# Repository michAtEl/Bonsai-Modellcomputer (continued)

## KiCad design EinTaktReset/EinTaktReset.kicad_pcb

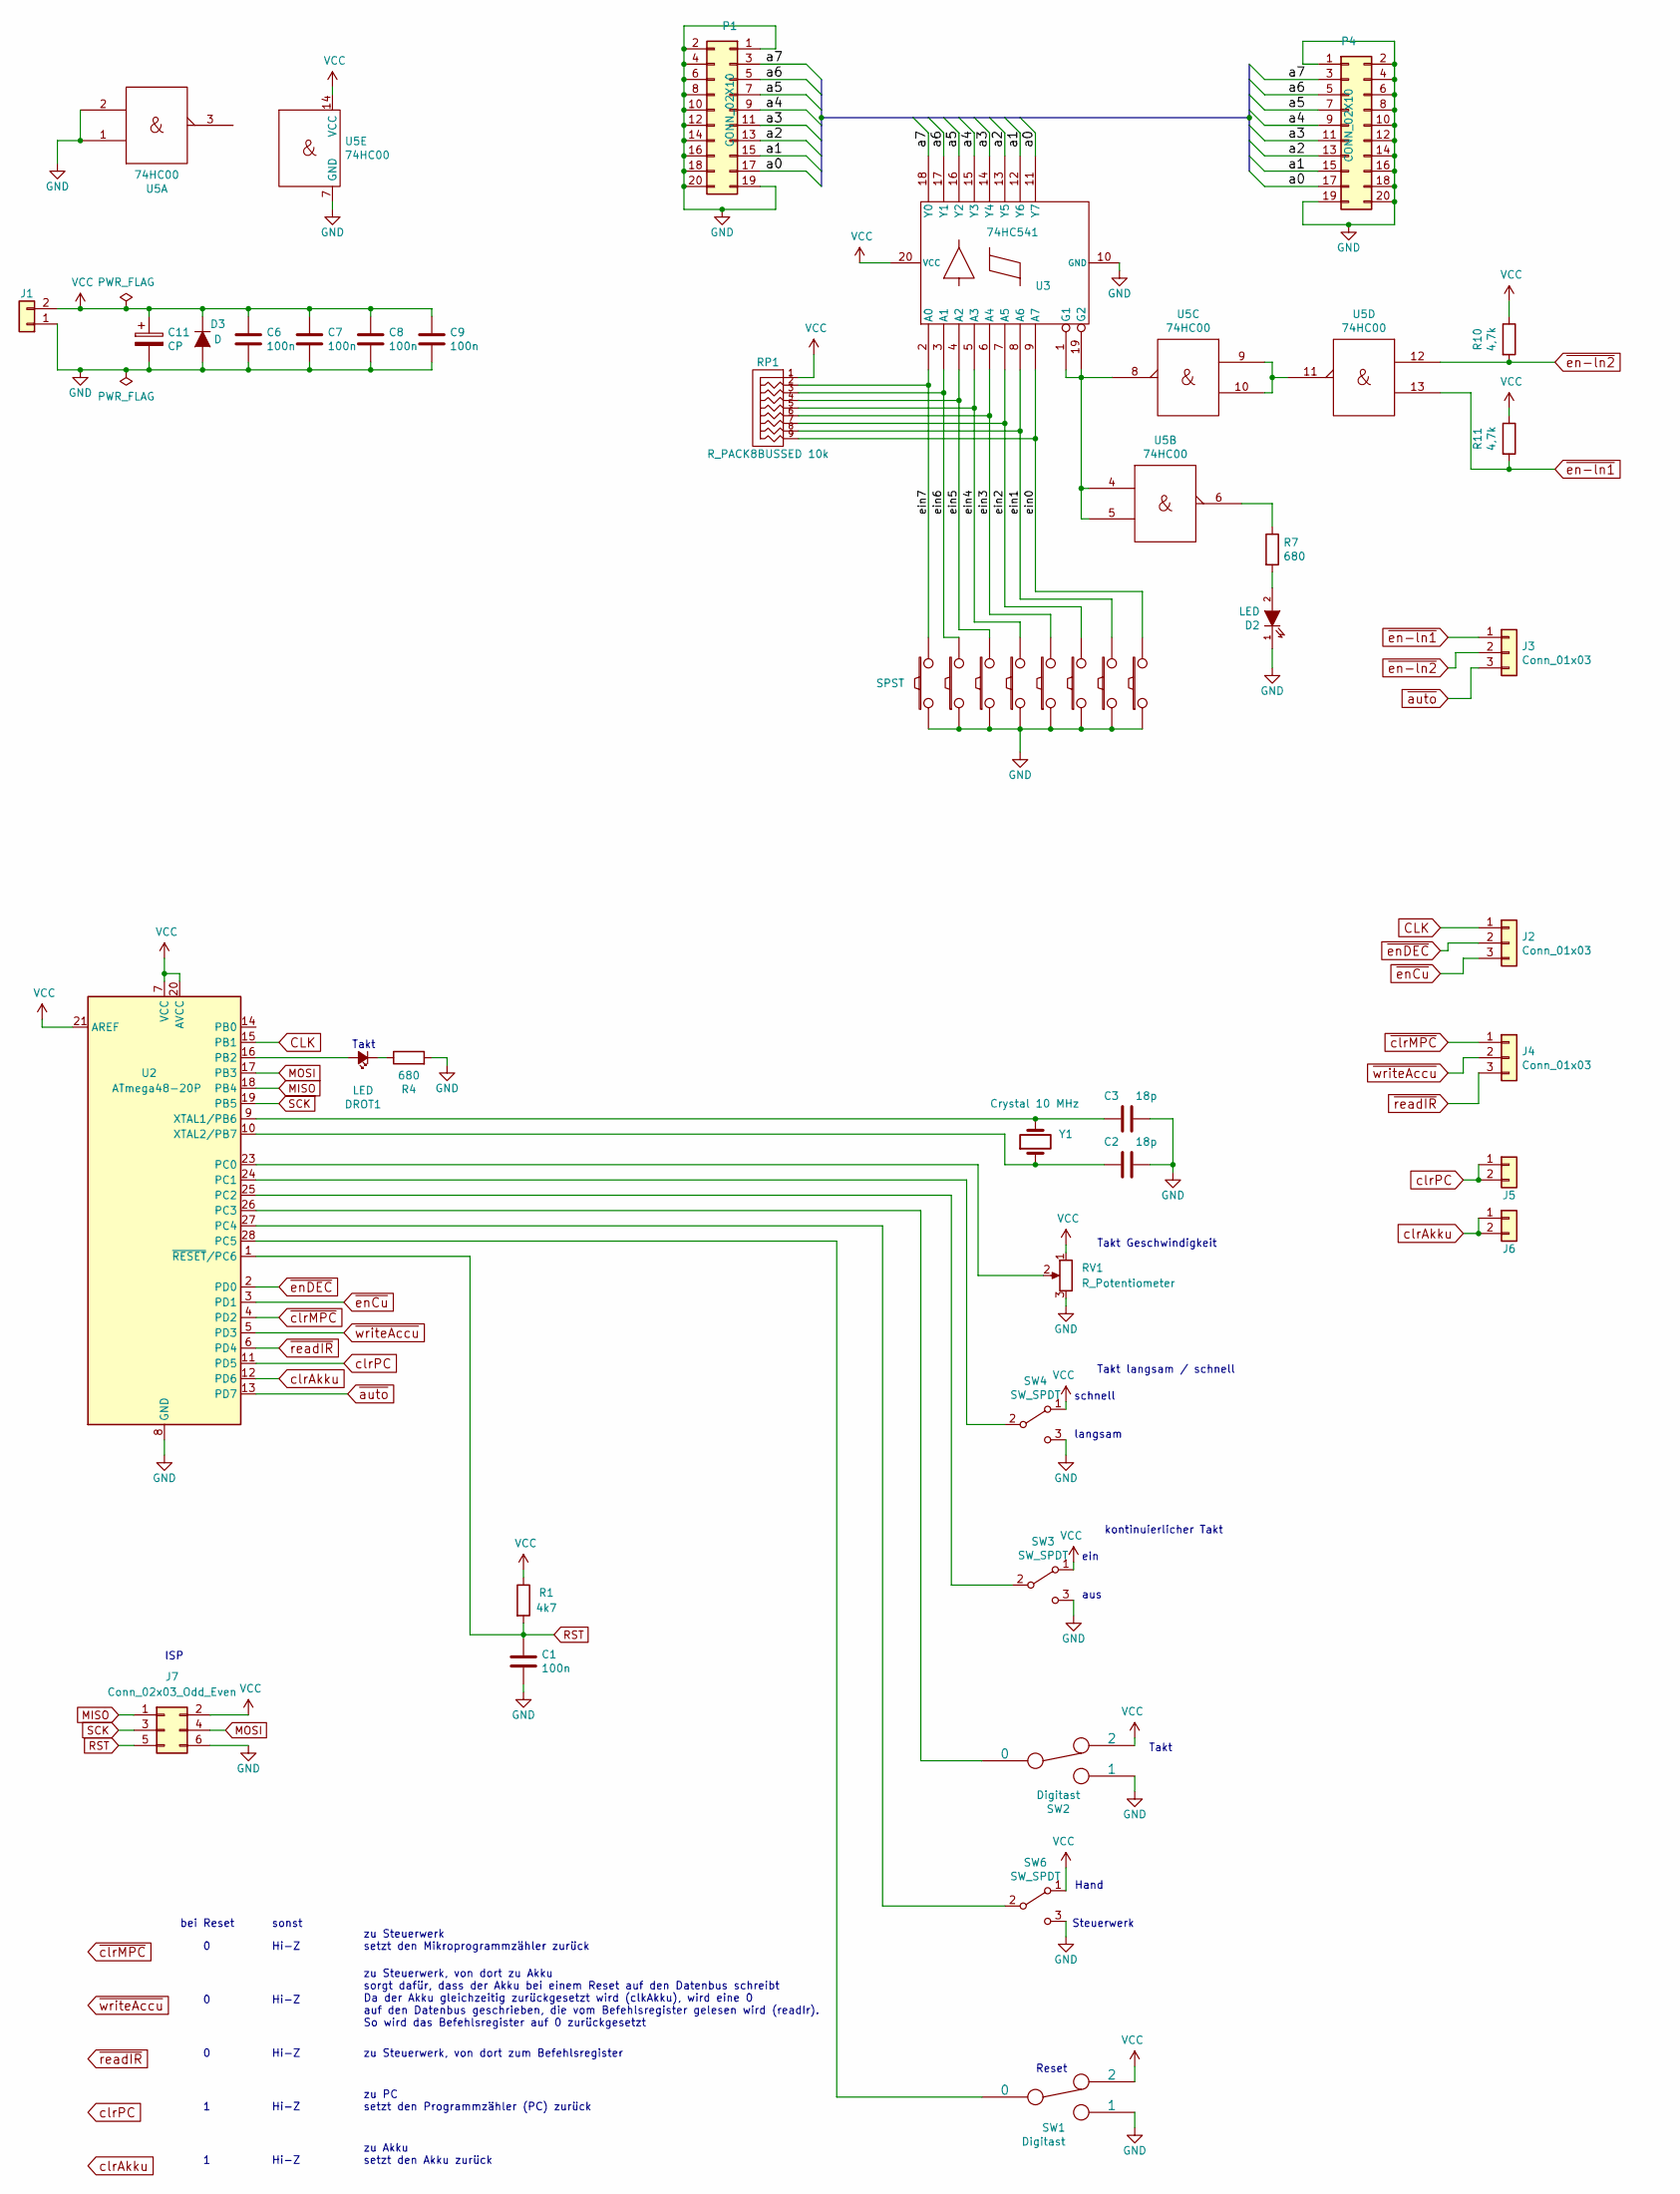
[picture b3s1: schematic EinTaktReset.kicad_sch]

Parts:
C1, C6, C7, C8, C9: 100n; C_Disc_D10.0mm_W2.5mm_P5.00mm
C2, C3: 18p; C_Disc_D3.8mm_W2.6mm_P2.50mm
C11: CP; CP_Radial_D8.0mm_P2.50mm
D2: LED; LED_D3.0mm
D3: D; D_A-405_P10.16mm_Horizontal
DROT1: LED; LED_D3.0mm
J1, J5, J6: Conn_01x02; Molex_KK-254_AE-6410-02A_1x02_P2.54mm_Vertical
J2, J3, J4: Conn_01x03; Molex_KK-254_AE-6410-03A_1x03_P2.54mm_Vertical
J7: Conn_02x03_Odd_Even; PinHeader_2x03_P2.54mm_Vertical
P1, P4: CONN_02X10; PinHeader_2x10_P2.54mm_Vertical
R1: 4k7; R_Axial_DIN0207_L6.3mm_D2.5mm_P10.16mm_Horizontal
R4, R7: 680; R_Axial_DIN0207_L6.3mm_D2.5mm_P10.16mm_Horizontal
R10, R11: 4,7k; R_Axial_DIN0207_L6.3mm_D2.5mm_P10.16mm_Horizontal
RP1: R_PACK8BUSSED 10k; R_Array_SIP9
RV1: R_Potentiometer; Potentiometer_Piher_PT-15-V02_Vertical
SW1, SW2: Digitast; Switch_Digitast
SW3, SW4, SW6: SW_SPDT; switch_100sp5
SW5, SW7, SW8, SW9, SW10, SW11, SW12, SW13: SPST; switch_100sp5
U2: ATmega48-20P; DIP-28_W7.62mm_LongPads
U3: 74HC541; DIP-20_W7.62mm_Socket_LongPads
U5: 74HC00; DIP-14_W7.62mm_Socket_LongPads
Y1: Crystal 10 MHz; Crystal_HC49-U_Vertical

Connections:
/a0: P1.17, P4.17, U3.11 (Y7)
/a1: P1.15, P4.15, U3.12 (Y6)
/a2: P1.13, P4.13, U3.13 (Y5)
/a3: P1.11, P4.11, U3.14 (Y4)
/a4: P1.9, P4.9, U3.15 (Y3)
/a5: P1.7, P4.7, U3.16 (Y2)
/a6: P1.5, P4.5, U3.17 (Y1)
/a7: P1.3, P4.3, U3.18 (Y0)
/ein0: RP1.9, SW13.2, U3.9 (A7)
/ein1: RP1.8, SW12.2, U3.8 (A6)
/ein2: RP1.7, SW11.2, U3.7 (A5)
/ein3: RP1.6, SW10.2, U3.6 (A4)
/ein4: RP1.5, SW9.2, U3.5 (A3)
/ein5: RP1.4, SW8.2, U3.4 (A2)
/ein6: RP1.3, SW7.2, U3.3 (A1)
/ein7: RP1.2, SW5.2, U3.2 (A0)
CLK: J2.1, U2.15 (PB1)
GND: C1.2, C2.2, C3.2, C6.2, C7.2, C8.2, C9.2, C11.2, D2.1 (K), D3.2 (A), J1.1, J7.6, P1.1, P1.2, P1.4, P1.6, P1.8, P1.10, P1.12, P1.14, P1.16, P1.18, P1.19, P1.20, P4.1, P4.2, P4.4, P4.6, P4.8, P4.10, P4.12, P4.14, P4.16, P4.18, P4.19, P4.20, R4.2, RV1.3, SW1.1, SW2.1, SW3.3 (C), SW4.3 (C), SW5.1, SW6.3 (C), SW7.1, SW8.1, SW9.1, SW10.1, SW11.1, SW12.1, SW13.1, U2.8 (GND), U2.22 (GND), U3.10 (GND), U5.1, U5.2, U5.7 (GND)
MISO: J7.1, U2.18 (PB4)
MOSI: J7.4, U2.17 (PB3)
unnamed: D2.2 (A), R7.2
unnamed: DROT1.2 (A), U2.16 (PB2)
unnamed: DROT1.1 (K), R4.1
unnamed: R7.1, U5.6
unnamed: SW3.2 (B), U2.25 (PC2)
unnamed: SW4.2 (B), U2.24 (PC1)
unnamed: SW6.2 (B), U2.27 (PC4)
unnamed: RV1.2, U2.23 (PC0)
unnamed: SW2.0, U2.26 (PC3)
unnamed: SW1.0, U2.28 (PC5)
unnamed: C3.1, U2.9 (XTAL1/PB6), Y1.2
unnamed: C2.1, U2.10 (XTAL2/PB7), Y1.1
unnamed: U3.1 (G1), U3.19 (G2), U5.4, U5.5, U5.8
unnamed: U5.9, U5.10, U5.11
RST: C1.1, J7.5, R1.2, U2.1 (~RESET/PC6)
SCK: J7.3, U2.19 (PB5)
VCC: C6.1, C7.1, C8.1, C9.1, C11.1, D3.1 (K), J1.2, J7.2, R1.1, R10.1, R11.1, RP1.1, RV1.1, SW1.2, SW2.2, SW3.1 (A), SW4.1 (A), SW6.1 (A), U2.7 (VCC), U2.20 (AVCC), U2.21 (AREF), U3.20 (VCC), U5.14 (VCC)
clrAkku: J6.1, J6.2, U2.12 (PD6)
clrPC: J5.1, J5.2, U2.11 (PD5)
~auto: J3.3, U2.13 (PD7)
~clrMPC: J4.1, U2.4 (PD2)
~en-ln1: J3.1, R11.2, U5.13
~en-ln2: J3.2, R10.2, U5.12
~enCu: J2.3, U2.3 (PD1)
~enDEC: J2.2, U2.2 (PD0)
~readIR: J4.3, U2.6 (PD4)
~writeAccu: J4.2, U2.5 (PD3)

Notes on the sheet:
Hand
Hi-Z
zu Steuerwerk, von dort zu Akku sorgt dafür, dass der Akku bei einem Reset auf den Datenbus schreibt Da der Akku gleichzeitig zurückgesetzt wird (clkAkku), wird eine 0 auf den Datenbus geschrieben, die vom Befehlsregister gelesen wird (readIr). So wird das Befehlsregister auf 0 zurückgesetzt
ein
zu PC setzt den Programmzähler (PC) zurück
langsam
bei Reset
zu Akku setzt den Akku zurück
Takt
Takt Geschwindigkeit
Takt langsam / schnell
aus
Steuerwerk
Reset
schnell
zu Steuerwerk, von dort zum Befehlsregister
kontinuierlicher Takt
zu Steuerwerk setzt den Mikroprogrammzähler zurück
ISP
sonst

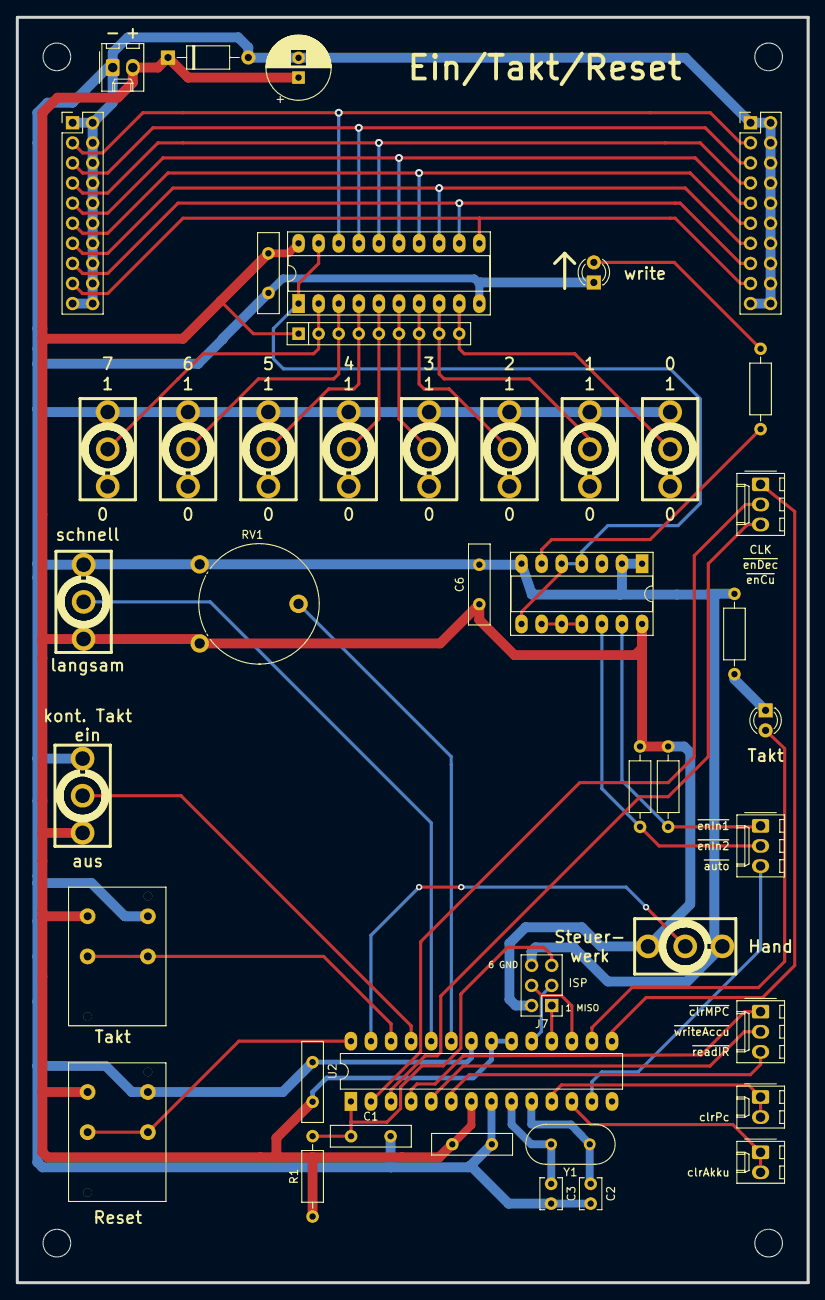
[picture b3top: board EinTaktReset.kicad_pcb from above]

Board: 2 copper layers, 100.0 x 160.0 mm, 44 parts (0 on the bottom side), 47 nets.

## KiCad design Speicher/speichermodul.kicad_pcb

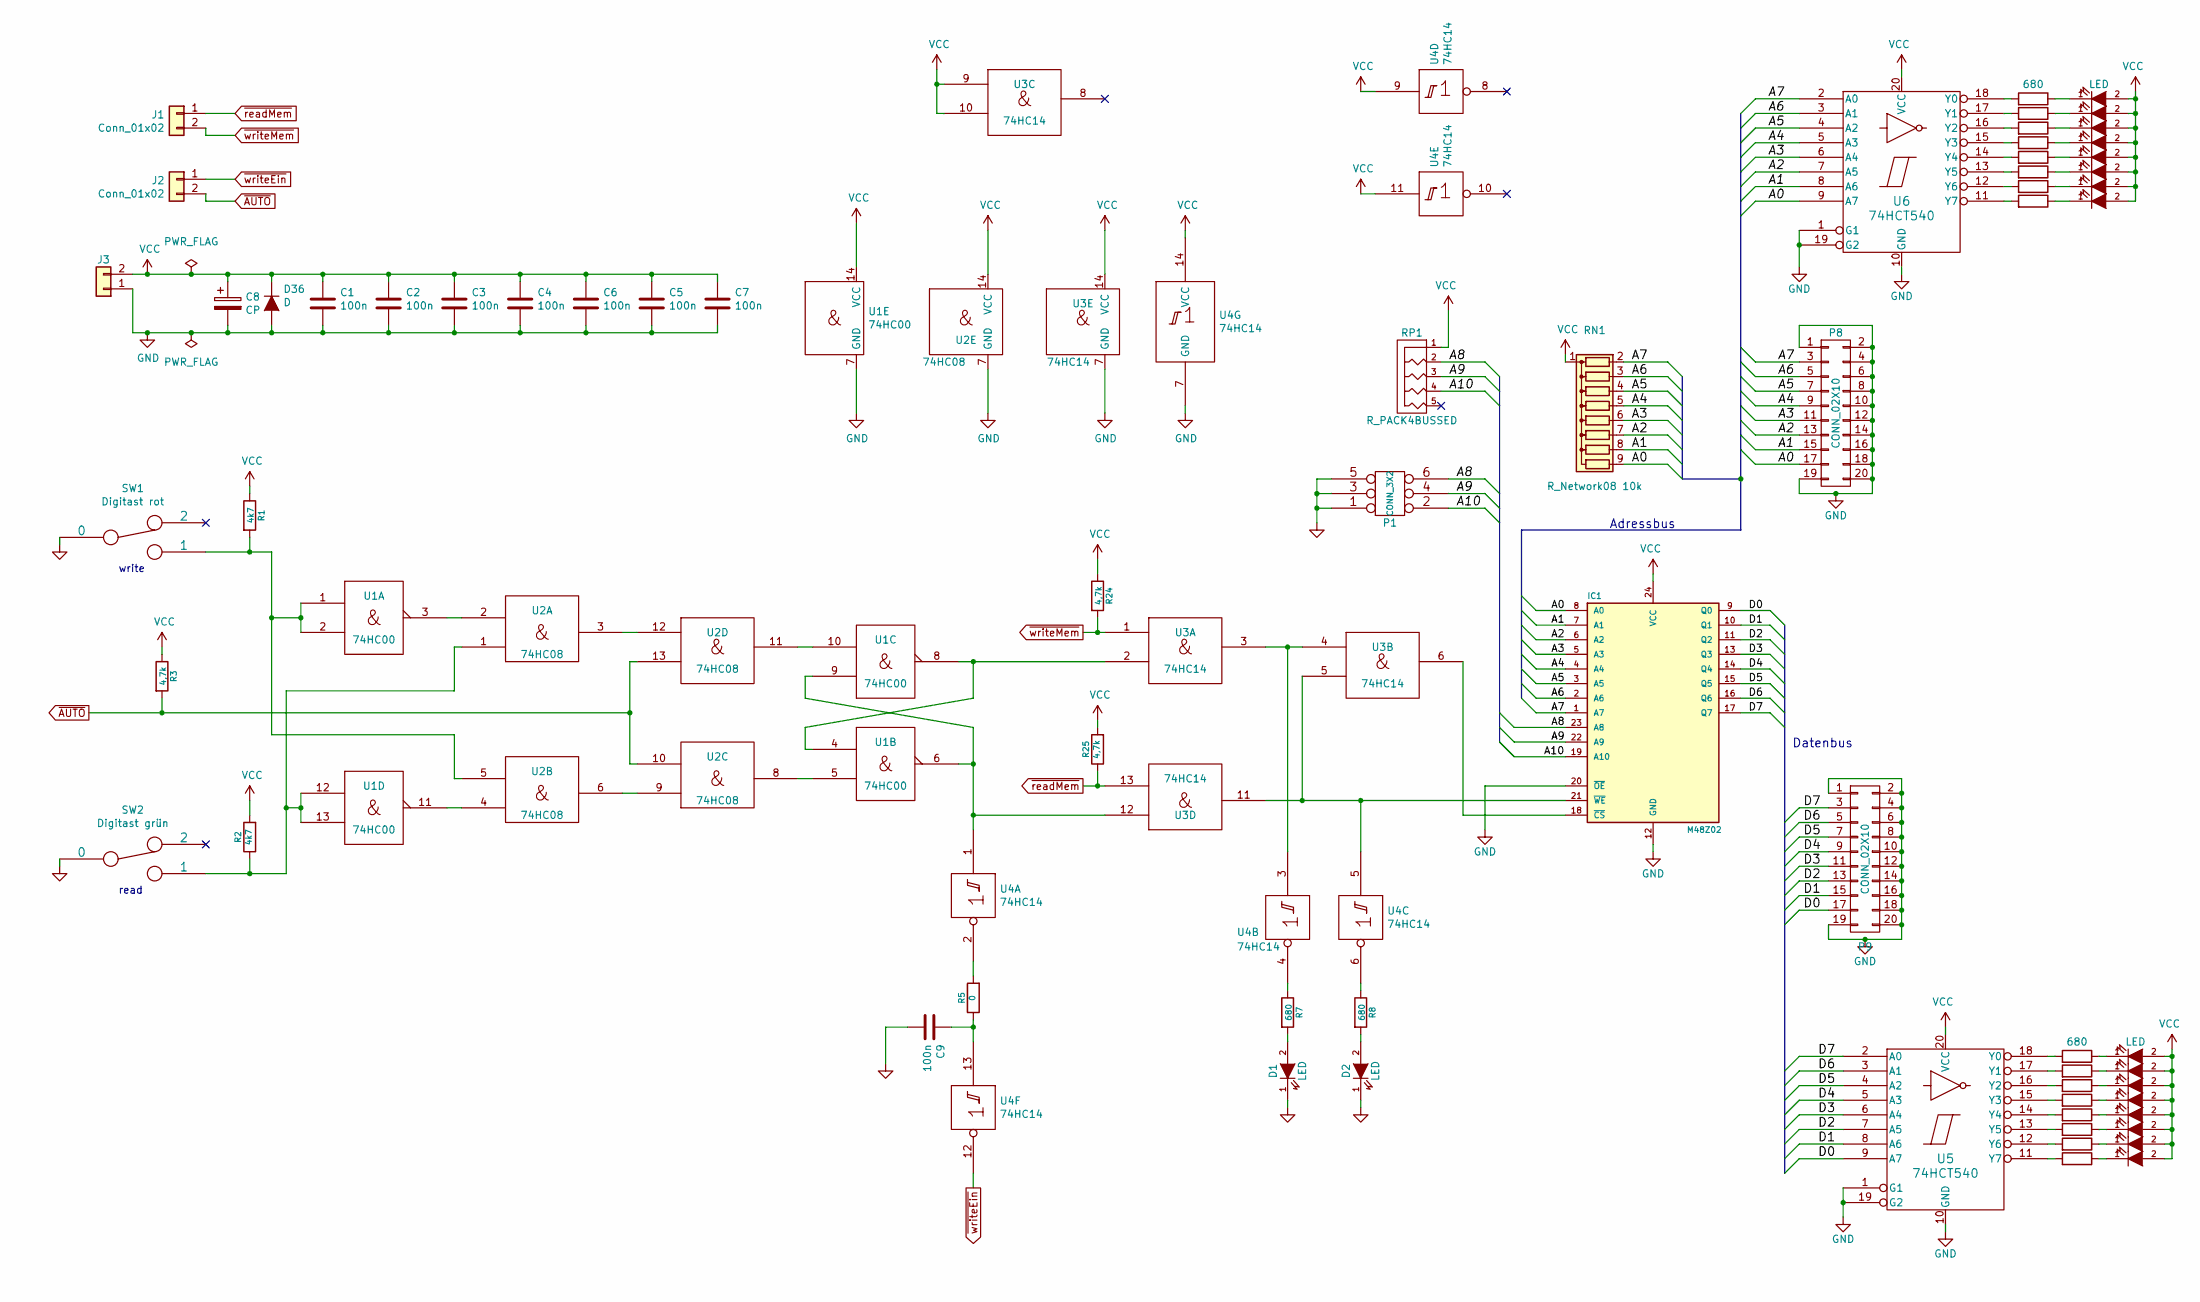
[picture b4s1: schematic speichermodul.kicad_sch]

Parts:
C1, C2, C3, C4, C5, C6, C7, C9: 100n; C_Disc_D10.0mm_W2.5mm_P5.00mm
C8: CP; CP_Radial_D8.0mm_P2.50mm
D1, D2, D3, D4, D5, D6, D7, D8, D9, D10, D11, D12, D13, D14, D15, D16, D17, D18: LED; LED_D3.0mm
D36: D; D_A-405_P10.16mm_Horizontal
IC1: M48Z02; DIP-24_W15.24mm_Socket_LongPads
J1, J2, J3: Conn_01x02; Molex_KK-254_AE-6410-02A_1x02_P2.54mm_Vertical
P1: CONN_3X2; PinHeader_2x03_P2.54mm_Vertical
P8, P9: CONN_02X10; PinHeader_2x10_P2.54mm_Vertical
R1, R2: 4k7; R_Axial_DIN0207_L6.3mm_D2.5mm_P10.16mm_Horizontal
R3, R24, R25: 4,7k; R_Axial_DIN0207_L6.3mm_D2.5mm_P10.16mm_Horizontal
R4, R7, R8, R9, R10, R11, R12, R13, R14, R15, R16, R17, R18, R19, R20, R21, R22, R23: 680; R_Axial_DIN0207_L6.3mm_D2.5mm_P10.16mm_Horizontal
R5: 0; R_Axial_DIN0207_L6.3mm_D2.5mm_P10.16mm_Horizontal
RN1: R_Network08 10k; R_Array_SIP9
RP1: R_PACK4BUSSED; R_Array_SIP5
SW1: Digitast rot; Switch_Digitast
SW2: Digitast grün; Switch_Digitast
U1: 74HC00; DIP-14_W7.62mm_Socket_LongPads
U2: 74HC08; DIP-14_W7.62mm_Socket_LongPads
U3, U4: 74HC14; DIP-14_W7.62mm_Socket_LongPads
U5, U6: 74HCT540; DIP-20_W7.62mm_Socket_LongPads

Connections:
/A0: IC1.8 (A0), P8.17, RN1.9 (R8), U6.9 (A7)
/A1: IC1.7 (A1), P8.15, RN1.8 (R7), U6.8 (A6)
/A2: IC1.6 (A2), P8.13, RN1.7 (R6), U6.7 (A5)
/A3: IC1.5 (A3), P8.11, RN1.6 (R5), U6.6 (A4)
/A4: IC1.4 (A4), P8.9, RN1.5 (R4), U6.5 (A3)
/A5: IC1.3 (A5), P8.7, RN1.4 (R3), U6.4 (A2)
/A6: IC1.2 (A6), P8.5, RN1.3 (R2), U6.3 (A1)
/A7: IC1.1 (A7), P8.3, RN1.2 (R1), U6.2 (A0)
/A8: IC1.23 (A8), P1.6, RP1.2
/A9: IC1.22 (A9), P1.4, RP1.3
/A10: IC1.19 (A10), P1.2, RP1.4
/D0: IC1.9 (Q0), P9.17, U5.9 (A7)
/D1: IC1.10 (Q1), P9.15, U5.8 (A6)
/D2: IC1.11 (Q2), P9.13, U5.7 (A5)
/D3: IC1.13 (Q3), P9.11, U5.6 (A4)
/D4: IC1.14 (Q4), P9.9, U5.5 (A3)
/D5: IC1.15 (Q5), P9.7, U5.4 (A2)
/D6: IC1.16 (Q6), P9.5, U5.3 (A1)
/D7: IC1.17 (Q7), P9.3, U5.2 (A0)
GND: C1.2, C2.2, C3.2, C4.2, C5.2, C6.2, C7.2, C8.2, C9.2, D1.1 (K), D2.1 (K), D36.2 (A), IC1.12 (GND), IC1.20 (~OE), J3.1, P1.1, P1.3, P1.5, P8.1, P8.2, P8.4, P8.6, P8.8, P8.10, P8.12, P8.14, P8.16, P8.18, P8.19, P8.20, P9.1, P9.2, P9.4, P9.6, P9.8, P9.10, P9.12, P9.14, P9.16, P9.18, P9.19, P9.20, SW1.0, SW2.0, U1.7 (GND), U2.7 (GND), U3.7 (GND), U4.7 (GND), U5.1 (G1), U5.10 (GND), U5.19 (G2), U6.1 (G1), U6.10 (GND), U6.19 (G2)
unnamed: C9.1, R5.1, U4.13
unnamed: D1.2 (A), R7.2
unnamed: D2.2 (A), R8.2
unnamed: D3.1 (K), R15.1
unnamed: D4.1 (K), R14.1
unnamed: D5.1 (K), R13.1
unnamed: D6.1 (K), R12.1
unnamed: D7.1 (K), R11.1
unnamed: D8.1 (K), R10.1
unnamed: D9.1 (K), R9.1
unnamed: D10.1 (K), R4.1
unnamed: D11.1 (K), R23.1
unnamed: D12.1 (K), R22.1
unnamed: D13.1 (K), R21.1
unnamed: D14.1 (K), R20.1
unnamed: D15.1 (K), R19.1
unnamed: D16.1 (K), R18.1
unnamed: D17.1 (K), R17.1
unnamed: D18.1 (K), R16.1
unnamed: IC1.18 (~CS), U3.6
unnamed: IC1.21 (~WE), U3.5, U3.11, U4.5
unnamed: R1.2, SW1.1, U1.1, U1.2, U2.5
unnamed: R2.1, SW2.1, U1.12, U1.13, U2.1
unnamed: R5.2, U4.2
unnamed: R7.1, U4.4
unnamed: R8.1, U4.6
unnamed: U1.3, U2.2
unnamed: U1.4, U1.8, U3.2
unnamed: U1.5, U2.8
unnamed: U1.6, U1.9, U3.12, U4.1
unnamed: U1.10, U2.11
unnamed: U1.11, U2.4
unnamed: U2.6, U2.9
unnamed: U2.3, U2.12
unnamed: U3.3, U3.4, U4.3
unnamed: R4.2, U5.18 (Y0)
unnamed: R9.2, U5.17 (Y1)
unnamed: R10.2, U5.16 (Y2)
unnamed: R11.2, U5.15 (Y3)
unnamed: R12.2, U5.14 (Y4)
unnamed: R13.2, U5.13 (Y5)
unnamed: R14.2, U5.12 (Y6)
unnamed: R15.2, U5.11 (Y7)
unnamed: R16.2, U6.18 (Y0)
unnamed: R17.2, U6.17 (Y1)
unnamed: R18.2, U6.16 (Y2)
unnamed: R19.2, U6.15 (Y3)
unnamed: R20.2, U6.14 (Y4)
unnamed: R21.2, U6.13 (Y5)
unnamed: R22.2, U6.12 (Y6)
unnamed: R23.2, U6.11 (Y7)
VCC: C1.1, C2.1, C3.1, C4.1, C5.1, C6.1, C7.1, C8.1, D3.2 (A), D4.2 (A), D5.2 (A), D6.2 (A), D7.2 (A), D8.2 (A), D9.2 (A), D10.2 (A), D11.2 (A), D12.2 (A), D13.2 (A), D14.2 (A), D15.2 (A), D16.2 (A), D17.2 (A), D18.2 (A), D36.1 (K), IC1.24 (VCC), J3.2, R1.1, R2.2, R3.1, R24.1, R25.2, RN1.1 (common), RP1.1, U1.14 (VCC), U2.14 (VCC), U3.9, U3.10, U3.14 (VCC), U4.9, U4.11, U4.14 (VCC), U5.20 (VCC), U6.20 (VCC)
~AUTO: J2.2, R3.2, U2.10, U2.13
~readMem: J1.1, R25.1, U3.13
~writeEin: J2.1, U4.12
~writeMem: J1.2, R24.2, U3.1

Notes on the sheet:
Adressbus
Datenbus
read
write

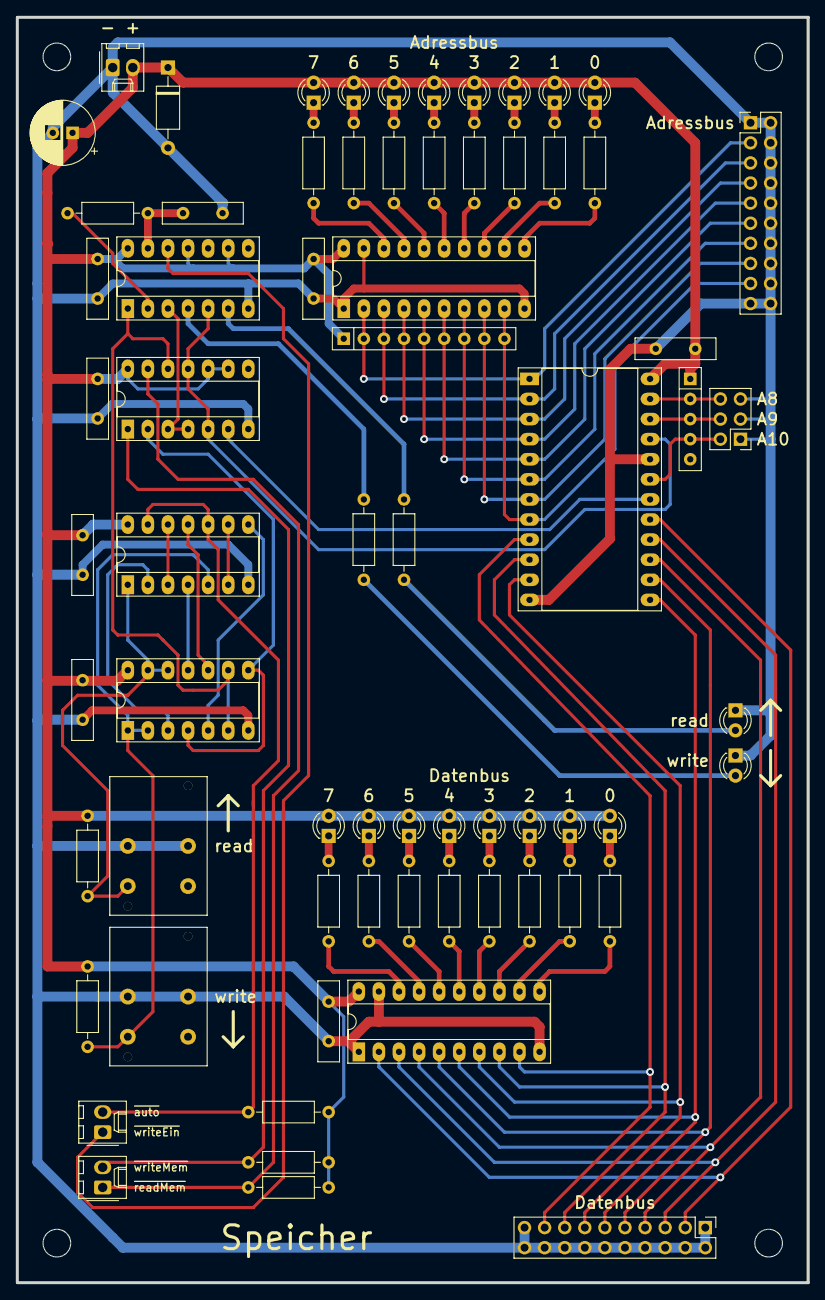
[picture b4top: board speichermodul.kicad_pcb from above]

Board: 2 copper layers, 100.0 x 160.0 mm, 69 parts (0 on the bottom side), 76 nets.

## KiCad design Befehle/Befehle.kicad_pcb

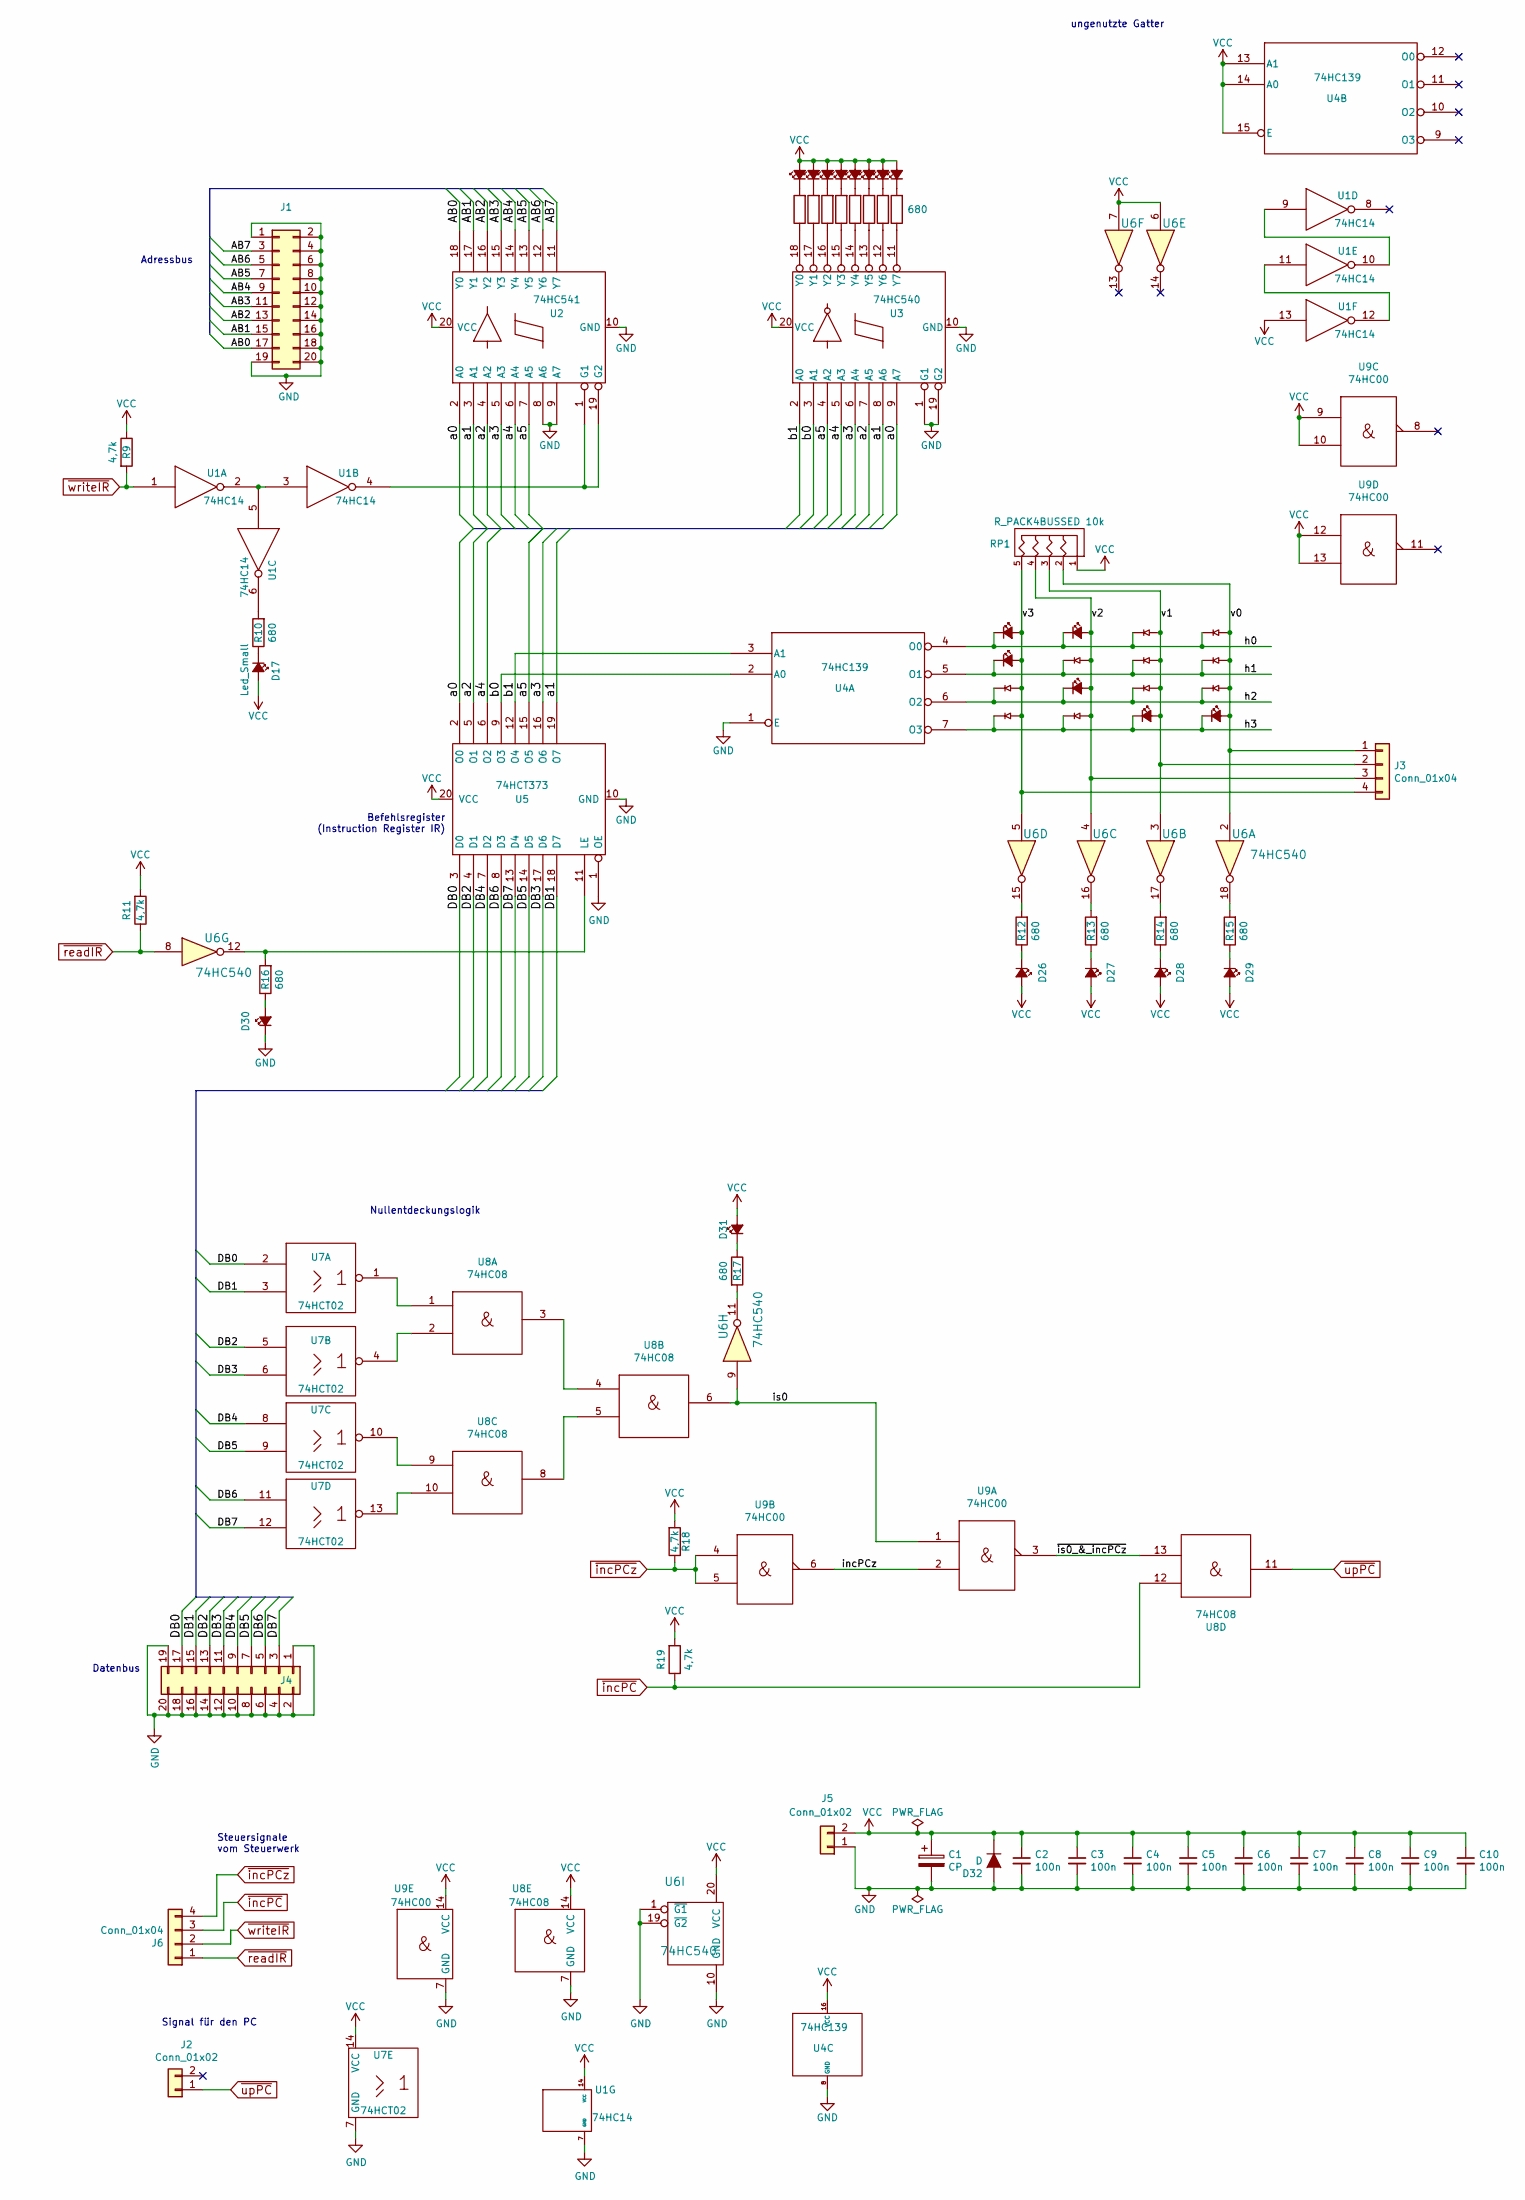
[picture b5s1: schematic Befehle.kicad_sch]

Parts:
C1: CP; CP_Radial_D8.0mm_P2.50mm
C2, C3, C4, C5, C6, C7, C8, C9, C10: 100n; C_Disc_D10.0mm_W2.5mm_P5.00mm
D1, D2, D3, D4, D5, D6, D7, D17: Led_Small; LED_D3.0mm
D8, D26, D27, D28, D29, D30, D31: LED; LED_D3.0mm
D9, D10, D13, D19, D24, D25: Led_Small; LED_Diodenmatrix
D11, D12, D14, D15, D16, D18, D20, D21, D22, D23: bonsai_Led_Small_Platzhalter; LED_Diodenmatrix_Platzhalter
D32: D; D_A-405_P10.16mm_Horizontal
J1, J4: Conn_02x10_Odd_Even; PinHeader_2x10_P2.54mm_Vertical
J2, J5: Conn_01x02; Molex_KK-254_AE-6410-02A_1x02_P2.54mm_Vertical
J3, J6: Conn_01x04; Molex_KK-254_AE-6410-04A_1x04_P2.54mm_Vertical
R1, R2, R3, R4, R5, R6, R7, R8, R10, R12, R13, R14, R15, R16, R17: 680; R_Axial_DIN0207_L6.3mm_D2.5mm_P10.16mm_Horizontal
R9, R11, R18, R19: 4,7k; R_Axial_DIN0207_L6.3mm_D2.5mm_P10.16mm_Horizontal
RP1: R_PACK4BUSSED 10k; R_Array_SIP5
U1: 74HC14; DIP-14_W7.62mm_Socket_LongPads
U2: 74HC541; DIP-20_W7.62mm_Socket_LongPads
U3, U6: 74HC540; DIP-20_W7.62mm_Socket_LongPads
U4: 74HC139; DIP-16_W7.62mm_Socket_LongPads
U5: 74HCT373; DIP-20_W7.62mm_Socket_LongPads
U7: 74HCT02; DIP-14_W7.62mm_Socket_LongPads
U8: 74HC08; DIP-14_W7.62mm_Socket_LongPads
U9: 74HC00; DIP-14_W7.62mm_Socket_LongPads

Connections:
/AB0: J1.17, U2.18 (Y0)
/AB1: J1.15, U2.17 (Y1)
/AB2: J1.13, U2.16 (Y2)
/AB3: J1.11, U2.15 (Y3)
/AB4: J1.9, U2.14 (Y4)
/AB5: J1.7, U2.13 (Y5)
/AB6: J1.5, U2.12 (Y6)
/AB7: J1.3, U2.11 (Y7)
/DB0: J4.17, U5.3 (D0), U7.2
/DB1: J4.15, U5.18 (D7), U7.3
/DB2: J4.13, U5.4 (D1), U7.5
/DB3: J4.11, U5.17 (D6), U7.6
/DB4: J4.9, U5.7 (D2), U7.8
/DB5: J4.7, U5.14 (D5), U7.9
/DB6: J4.5, U5.8 (D3), U7.11
/DB7: J4.3, U5.13 (D4), U7.12
/a0: U2.2 (A0), U3.9 (A7), U5.2 (O0)
/a1: U2.3 (A1), U3.8 (A6), U5.19 (O7)
/a2: U2.4 (A2), U3.7 (A5), U5.5 (O1)
/a3: U2.5 (A3), U3.6 (A4), U5.16 (O6)
/a4: U2.6 (A4), U3.5 (A3), U5.6 (O2)
/a5: U2.7 (A5), U3.4 (A2), U5.15 (O5)
/b0: U3.3 (A1), U4.2 (A0), U5.9 (O3)
/b1: U3.2 (A0), U4.3 (A1), U5.12 (O4)
/h0: D9.1 (K), D10.1 (K), D11.1 (K), D12.1 (K), U4.4 (O0)
/h1: D13.1 (K), D14.1 (K), D15.1 (K), D16.1 (K), U4.5 (O1)
/h2: D18.1 (K), D19.1 (K), D20.1 (K), D21.1 (K), U4.6 (O2)
/h3: D22.1 (K), D23.1 (K), D24.1 (K), D25.1 (K), U4.7 (O3)
/incPCz: U9.2, U9.6
/is0: U6.9, U8.6, U9.1
/v0: D12.2 (A), D16.2 (A), D21.2 (A), D25.2 (A), J3.1, RP1.2, U6.2
/v1: D11.2 (A), D15.2 (A), D20.2 (A), D24.2 (A), J3.2, RP1.3, U6.3
/v2: D10.2 (A), D14.2 (A), D19.2 (A), D23.2 (A), J3.3, RP1.4, U6.4
/v3: D9.2 (A), D13.2 (A), D18.2 (A), D22.2 (A), J3.4, RP1.5, U6.5
/~is0_&_incPCz: U8.13, U9.3
GND: C1.2, C2.2, C3.2, C4.2, C5.2, C6.2, C7.2, C8.2, C9.2, C10.2, D30.1 (K), D32.2 (A), J1.1, J1.2, J1.4, J1.6, J1.8, J1.10, J1.12, J1.14, J1.16, J1.18, J1.19, J1.20, J4.1, J4.2, J4.4, J4.6, J4.8, J4.10, J4.12, J4.14, J4.16, J4.18, J4.19, J4.20, J5.1, U1.7 (GND), U2.8 (A6), U2.9 (A7), U2.10 (GND), U3.1 (G1), U3.10 (GND), U3.19 (G2), U4.1 (E), U4.8 (GND), U5.1 (OE), U5.10 (GND), U6.1 (~G1), U6.10 (GND), U6.19 (~G2), U7.7 (GND), U8.7 (GND), U9.7 (GND)
unnamed: D1.1 (K), R1.2
unnamed: D2.1 (K), R2.2
unnamed: D3.1 (K), R3.2
unnamed: D4.1 (K), R4.2
unnamed: D5.1 (K), R5.2
unnamed: D6.1 (K), R6.2
unnamed: D7.1 (K), R7.2
unnamed: D8.1 (K), R8.2
unnamed: D17.1 (K), R10.1
unnamed: D26.1 (K), R12.1
unnamed: D27.1 (K), R13.1
unnamed: D28.1 (K), R14.1
unnamed: D29.1 (K), R15.1
unnamed: D30.2 (A), R16.1
unnamed: D31.1 (K), R17.1
unnamed: R10.2, U1.6
unnamed: R12.2, U6.15
unnamed: R13.2, U6.16
unnamed: R14.2, U6.17
unnamed: R15.2, U6.18
unnamed: R17.2, U6.11
unnamed: U1.2, U1.3, U1.5
unnamed: U1.9, U1.10
unnamed: U1.11, U1.12
unnamed: U1.4, U2.1 (G1), U2.19 (G2)
unnamed: R1.1, U3.18 (Y0)
unnamed: R2.1, U3.17 (Y1)
unnamed: R3.1, U3.16 (Y2)
unnamed: R4.1, U3.15 (Y3)
unnamed: R5.1, U3.14 (Y4)
unnamed: R6.1, U3.13 (Y5)
unnamed: R7.1, U3.12 (Y6)
unnamed: R8.1, U3.11 (Y7)
unnamed: R16.2, U5.11 (LE), U6.12
unnamed: U7.1, U8.1
unnamed: U7.4, U8.2
unnamed: U7.10, U8.9
unnamed: U7.13, U8.10
unnamed: U8.3, U8.4
unnamed: U8.5, U8.8
VCC: C1.1, C2.1, C3.1, C4.1, C5.1, C6.1, C7.1, C8.1, C9.1, C10.1, D1.2 (A), D2.2 (A), D3.2 (A), D4.2 (A), D5.2 (A), D6.2 (A), D7.2 (A), D8.2 (A), D17.2 (A), D26.2 (A), D27.2 (A), D28.2 (A), D29.2 (A), D31.2 (A), D32.1 (K), J5.2, R9.1, R11.2, R18.2, R19.2, RP1.1, U1.13, U1.14 (VCC), U2.20 (VCC), U3.20 (VCC), U4.13 (A1), U4.14 (A0), U4.15 (E), U4.16 (VCC), U5.20 (VCC), U6.6, U6.7, U6.20 (VCC), U7.14 (VCC), U8.14 (VCC), U9.9, U9.10, U9.12, U9.13, U9.14 (VCC)
~incPCz: J6.4, R18.1, U9.4, U9.5
~incPC: J6.3, R19.1, U8.12
~readIR: J6.1, R11.1, U6.8
~upPC: J2.1, U8.11
~writeIR: J6.2, R9.2, U1.1

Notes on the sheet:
Befehlsregister (Instruction Register IR)
Nullentdeckungslogik
ungenutzte Gatter
Steuersignale vom Steuerwerk
Signal für den PC
Adressbus
Datenbus

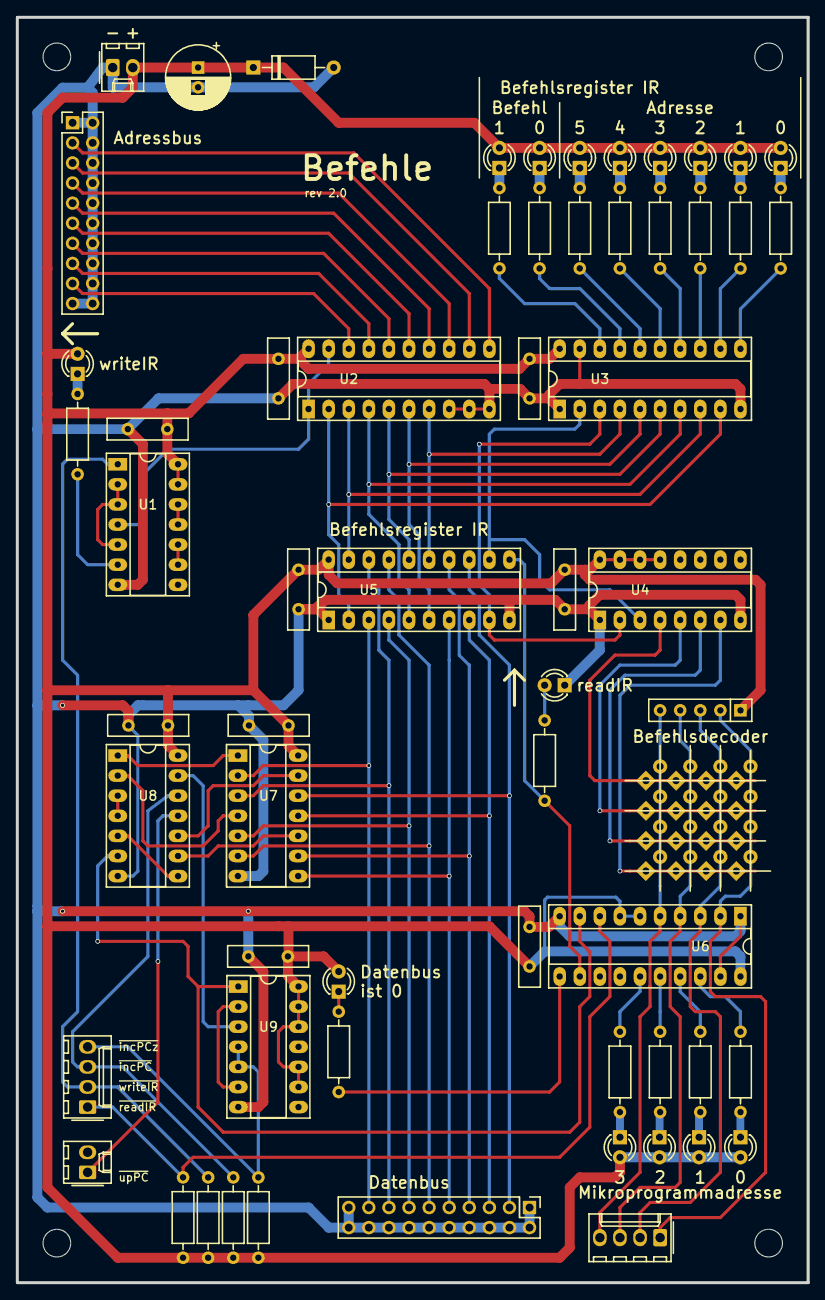
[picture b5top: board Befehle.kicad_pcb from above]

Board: 2 copper layers, 100.0 x 160.0 mm, 77 parts (0 on the bottom side), 82 nets.

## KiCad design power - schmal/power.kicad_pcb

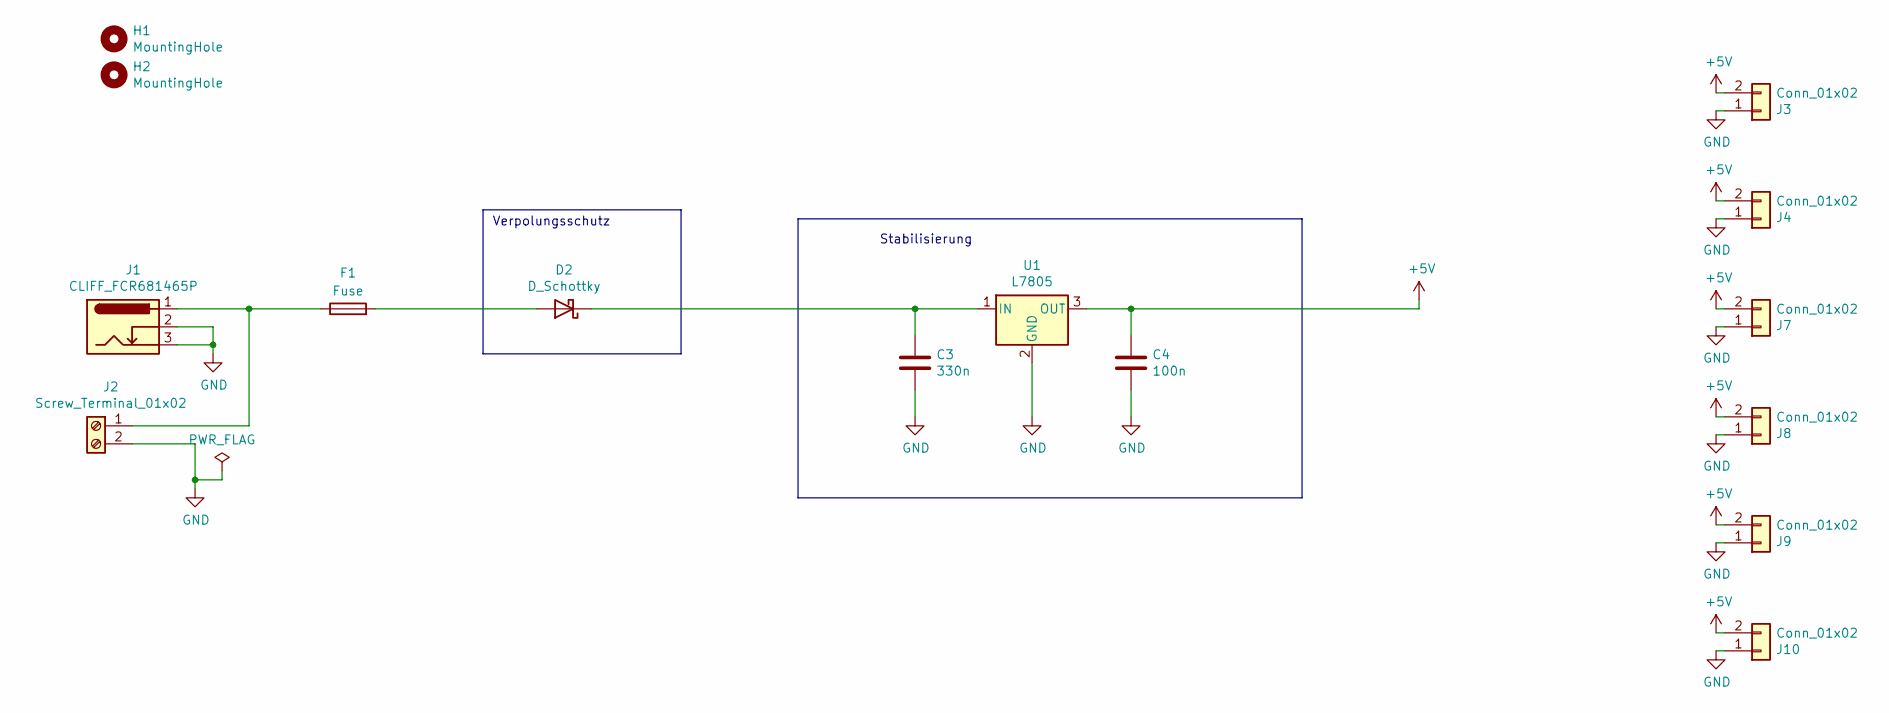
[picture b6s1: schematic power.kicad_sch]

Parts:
C3: 330n; C_Rect_L7.2mm_W2.2mm_P2.54mm_P5.08mm
C4: 100n; C_Rect_L7.2mm_W2.2mm_P2.54mm_P5.08mm
D2: D_Schottky; D_DO-201AE_P12.70mm_Horizontal
F1: Fuse; Sicherungshalter
H1, H2: MountingHole; MountingHole_3.5mm
J1: CLIFF_FCR681465P
J2: Screw_Terminal_01x02; TerminalBlock_Phoenix_MKDS-1,5-2-5.08_1x02_P5.08mm_Horizont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
J3, J4, J7, J8, J9, J10: Conn_01x02; Molex_KK-254_AE-6410-02A_1x02_P2.54mm_Vertical
U1: L7805; TO-220-3_Vertical

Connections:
+5V: C4.1, J3.2, J4.2, J7.2, J8.2, J9.2, J10.2, U1.3 (OUT)
GND: C3.2, C4.2, J1.2, J1.3, J2.2, J3.1, J4.1, J7.1, J8.1, J9.1, J10.1, U1.2 (GND)
unnamed: D2.2 (A), F1.2
unnamed: C3.1, D2.1 (K), U1.1 (IN)
unnamed: F1.1, J1.1, J2.1

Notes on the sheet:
Verpolungsschutz
Stabilisierung
